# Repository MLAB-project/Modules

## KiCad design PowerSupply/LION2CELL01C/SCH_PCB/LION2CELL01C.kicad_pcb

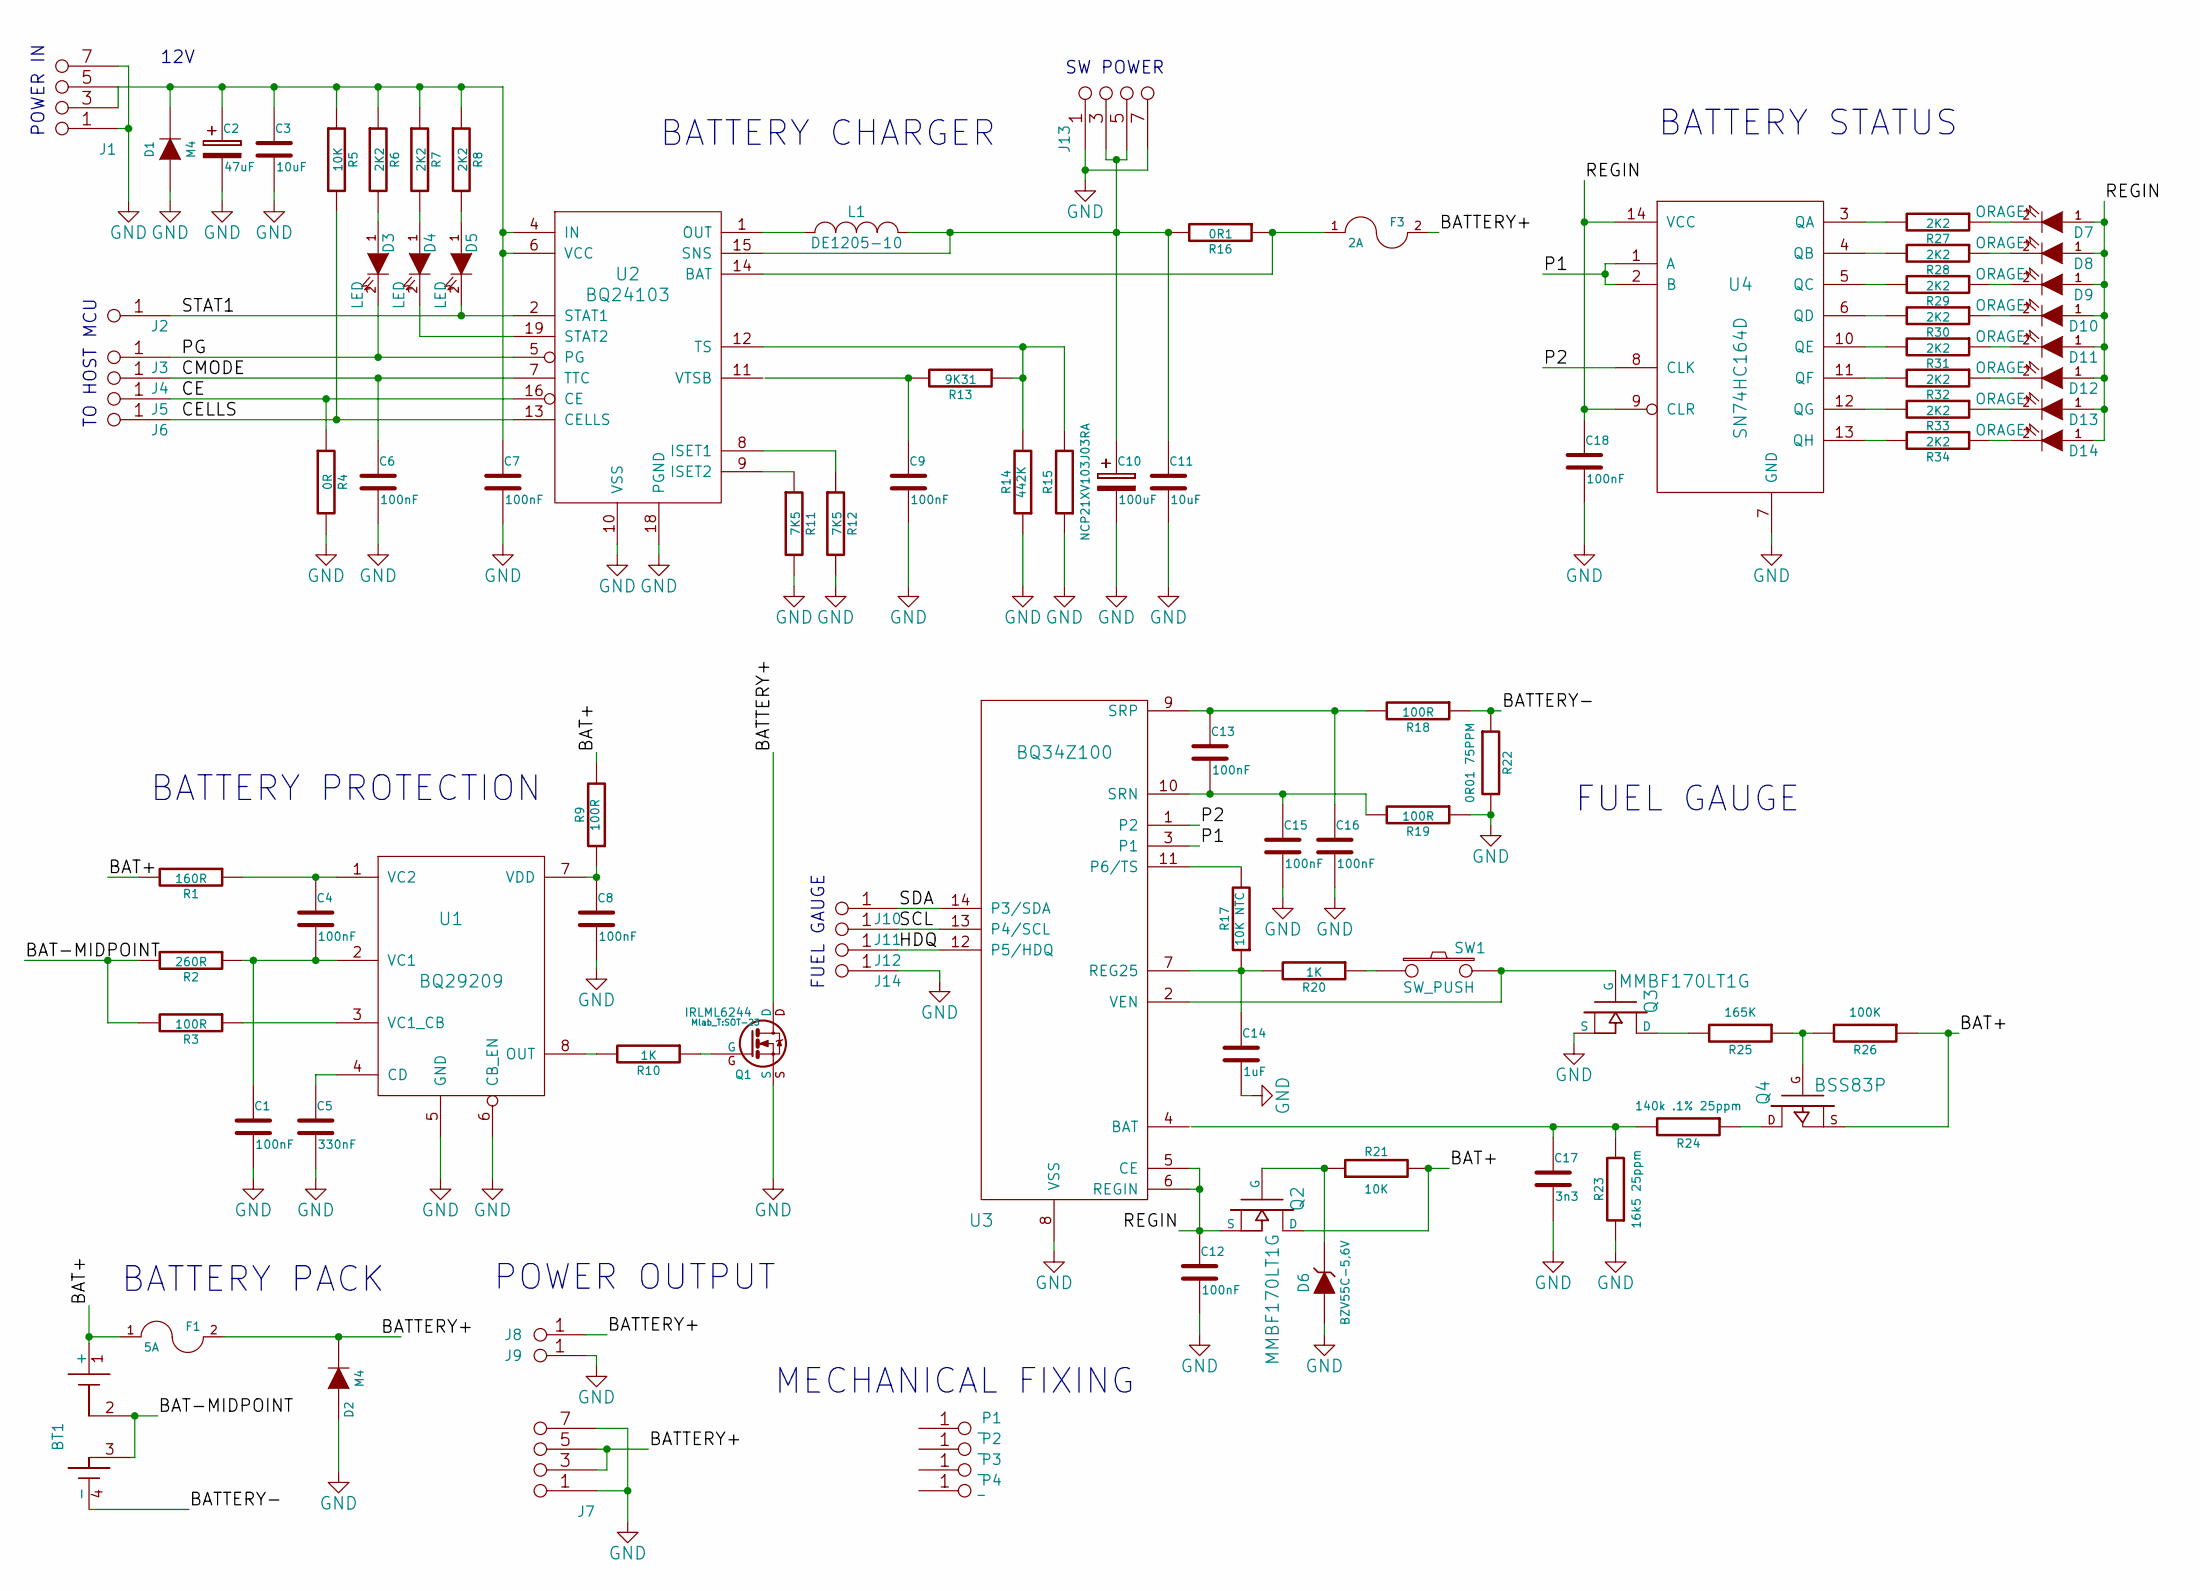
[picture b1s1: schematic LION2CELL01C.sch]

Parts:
BT1: 2x18650_LION-RESCUE-LION2CELL01C; 2LION
C1, C4, C6, C7, C8, C9, C12, C13, C15, C16, C18: 100nF; SMD-0805
C2: 47uF; TantalC_SizeC_Reflow
C3, C11: 10uF; SMD-0805
C5: 330nF; SMD-0805
C10: 100uF; TantalC_SizeD_Reflow
C14: 1uF; SMD-0805
C17: 3n3; SMD-0805
D1, D2: M4; SMA_Standard
D3, D4, D5: LED; LED_1206
D6: BZV55C-5,6V; MiniMELF_Standard
D7, D8, D9, D10, D11, D12, D13, D14: ORAGE; LED_1206
F1: 5A; Drzak_2410
F3: 2A; Drzak_2410
J1, J7, J13: JUMP_4X2; Straight_2x04
J2, J3, J4, J5, J6, J10, J11, J12, J14: JUMP_2x1; Straight_1x02
J8, J9: CONN1_1; WAGO256
L1: DE1205-10
P1, P2, P3, P4: _; MountingHole_3mm
Q1: IRLML6244; SOT-23
Q2, Q3: MMBF170LT1G; SOT-23
Q4: BSS83P; SOT-23
R1: 160R; SMD-0805
R2: 260R; SMD-0805
R3, R9, R18, R19: 100R; SMD-0805
R4: 0R; SMD-0805
R5, R21: 10K; SMD-0805
R6, R7, R8, R27, R28, R29, R30, R31, R32, R33, R34: 2K2; SMD-0805
R10, R20: 1K; SMD-0805
R11, R12: 7K5; SMD-0805
R13: 9K31; SMD-0805
R14: 442K; SMD-0805
R15: NCP21XV103J03RA; SMD-0805
R16: 0R1; R_2512
R17: 10K NTC; SMD-0805
R22: 0R01 75PPM; SMD-1206
R23: 16k5 25ppm; SMD-0805
R24: 140k .1% 25ppm; SMD-0805
R25: 165K; SMD-0805
R26: 100K; SMD-0805
SW1: SW_PUSH; SW_PUSH_SMALL
U1: BQ29209; VSON-8
U2: BQ24103; VQFN-20
U3: BQ34Z100; TSSOP-14_4.4x5mm_Pitch0.65mm
U4: SN74HC164D; SO-14

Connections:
/BAT+: BT1.1 (+), F1.1, Q2.D, Q4.S, R1.2, R9.2, R21.2, R26.1
/BAT-MIDPOINT: BT1.2, BT1.3, R2.2, R3.2
/BATTERY+: D2.2 (K), F1.2, F3.2, J7.3 (4), J7.4, J7.5, J7.6 (5), J8.1, Q1.D
/BATTERY-: BT1.4 (-), R18.1, R22.1
/CE: J5.1, J5.2, R4.1, U2.16 (CE)
/CELLS: J6.1, J6.2, R5.2, U2.13 (CELLS)
/CMODE: C6.1, J4.1, J4.2, U2.7 (TTC)
/HDQ: J12.1, J12.2, U3.12 (P5/HDQ)
/P1: U3.3 (P1), U4.1 (A), U4.2 (B)
/P2: U3.1 (P2), U4.8 (CLK)
/PG: D3.2 (K), J3.1, J3.2, U2.5 (PG)
/REGIN: C12.1, C18.1, D7.1 (A), D8.1 (A), D9.1 (A), D10.1 (A), D11.1 (A), D12.1 (A), D13.1 (A), D14.1 (A), Q2.S, U3.5 (CE), U3.6 (REGIN), U4.9 (CLR), U4.14 (VCC)
/SCL: J11.1, J11.2, U3.13 (P4/SCL)
/SDA: J10.1, J10.2, U3.14 (P3/SDA)
/STAT1: D5.2 (K), J2.1, J2.2, U2.2 (STAT1)
GND: C1.2, C2.2, C3.2, C5.2, C6.2, C7.2, C8.2, C9.2, C10.2, C11.2, C12.2, C14.2, C15.2, C16.2, C17.2, C18.2, D1.1 (A), D2.1 (A), D6.1 (A), J1.1 (2), J1.2, J1.7 (8), J1.8, J7.1 (2), J7.2, J7.7 (8), J7.8, J9.1, J13.1 (2), J13.2, J13.7 (8), J13.8, J14.1, J14.2, Q1.S, Q3.S, R4.2, R11.2, R12.2, R14.1, R15.1, R19.1, R22.2, R23.1, U1.5 (GND), U1.6 (CB_EN), U1.9 (GND), U2.10 (VSS), U2.17 (PGND), U2.18 (PGND), U2.21 (pgnd), U3.8 (VSS), U4.7 (GND)
unnamed: C1.1, C4.2, R2.1, U1.2 (VC1)
unnamed: C2.1, C3.1, C7.1, D1.2 (K), J1.3 (4), J1.4, J1.5, J1.6 (5), R5.1, R6.1, R7.1, R8.1, U2.3 (IN), U2.4 (IN), U2.6 (VCC)
unnamed: C4.1, R1.1, U1.1 (VC2)
unnamed: C5.1, U1.4 (CD)
unnamed: C8.1, R9.1, U1.7 (VDD)
unnamed: C9.1, R13.2
unnamed: C10.1, C11.1, J13.3 (4), J13.4, J13.5, J13.6 (5), L1.2, R16.2, U2.15 (SNS)
unnamed: C13.1, C16.1, R18.2, U3.9 (SRP)
unnamed: C13.2, C15.1, R19.2, U3.10 (SRN)
unnamed: C14.1, R17.1, R20.2, U3.7 (REG25)
unnamed: C17.1, R23.2, R24.2
unnamed: D3.1 (A), R6.2
unnamed: D4.1 (A), R7.2
unnamed: D4.2 (K), U2.19 (STAT2)
unnamed: D5.1 (A), R8.2
unnamed: D6.2 (K), Q2.G, R21.1
unnamed: D7.2 (K), R27.1
unnamed: D8.2 (K), R28.1
unnamed: D9.2 (K), R29.1
unnamed: D10.2 (K), R30.1
unnamed: D11.2 (K), R31.1
unnamed: D12.2 (K), R32.1
unnamed: D13.2 (K), R33.1
unnamed: D14.2 (K), R34.1
unnamed: F3.1, R16.1, U2.14 (BAT)
unnamed: L1.1, U2.1 (OUT), U2.20 (OUT)
unnamed: Q1.G, R10.1
unnamed: Q3.D, R25.2
unnamed: Q3.G, SW1.2, U3.2 (VEN)
unnamed: Q4.D, R24.1
unnamed: Q4.G, R25.1, R26.2
unnamed: R3.1, U1.3 (VC1_CB)
unnamed: R10.2, U1.8 (OUT)
unnamed: R11.1, U2.9 (ISET2)
unnamed: R12.1, U2.8 (ISET1)
unnamed: R13.1, R14.2, R15.2, U2.12 (TS)
unnamed: R17.2, U3.11 (P6/TS)
unnamed: R20.1, SW1.1
unnamed: R27.2, U4.3 (QA)
unnamed: R28.2, U4.4 (QB)
unnamed: R29.2, U4.5 (QC)
unnamed: R30.2, U4.6 (QD)
unnamed: R31.2, U4.10 (QE)
unnamed: R32.2, U4.11 (QF)
unnamed: R33.2, U4.12 (QG)
unnamed: R34.2, U4.13 (QH)

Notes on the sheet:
BATTERY PACK
BATTERY CHARGER
SW POWER
POWER IN
TO HOST MCU
BATTERY PROTECTION
FUEL GAUGE
POWER OUTPUT
MECHANICAL FIXING
BATTERY STATUS
12V

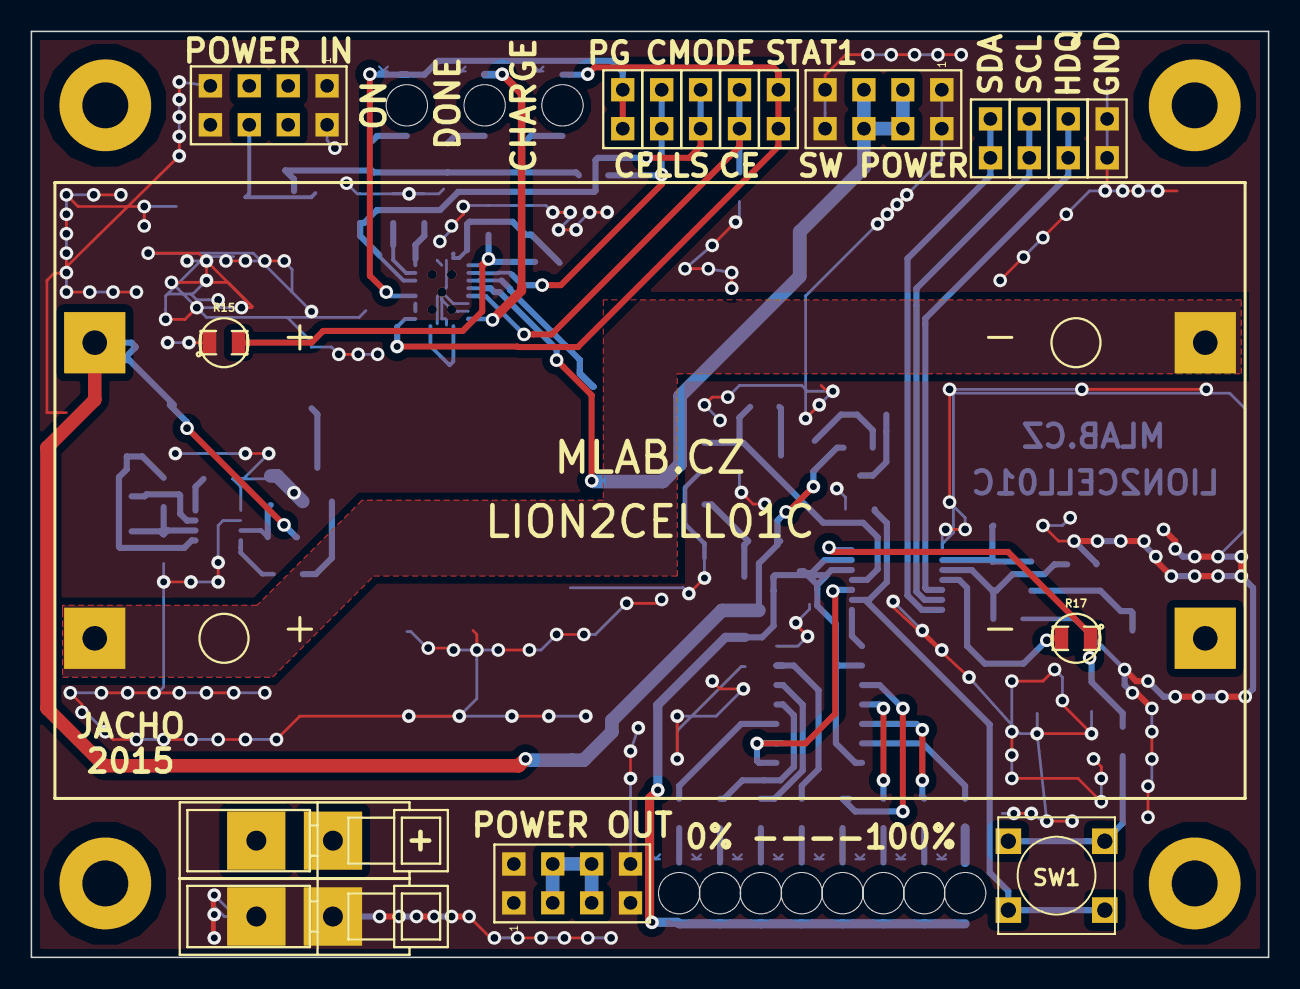
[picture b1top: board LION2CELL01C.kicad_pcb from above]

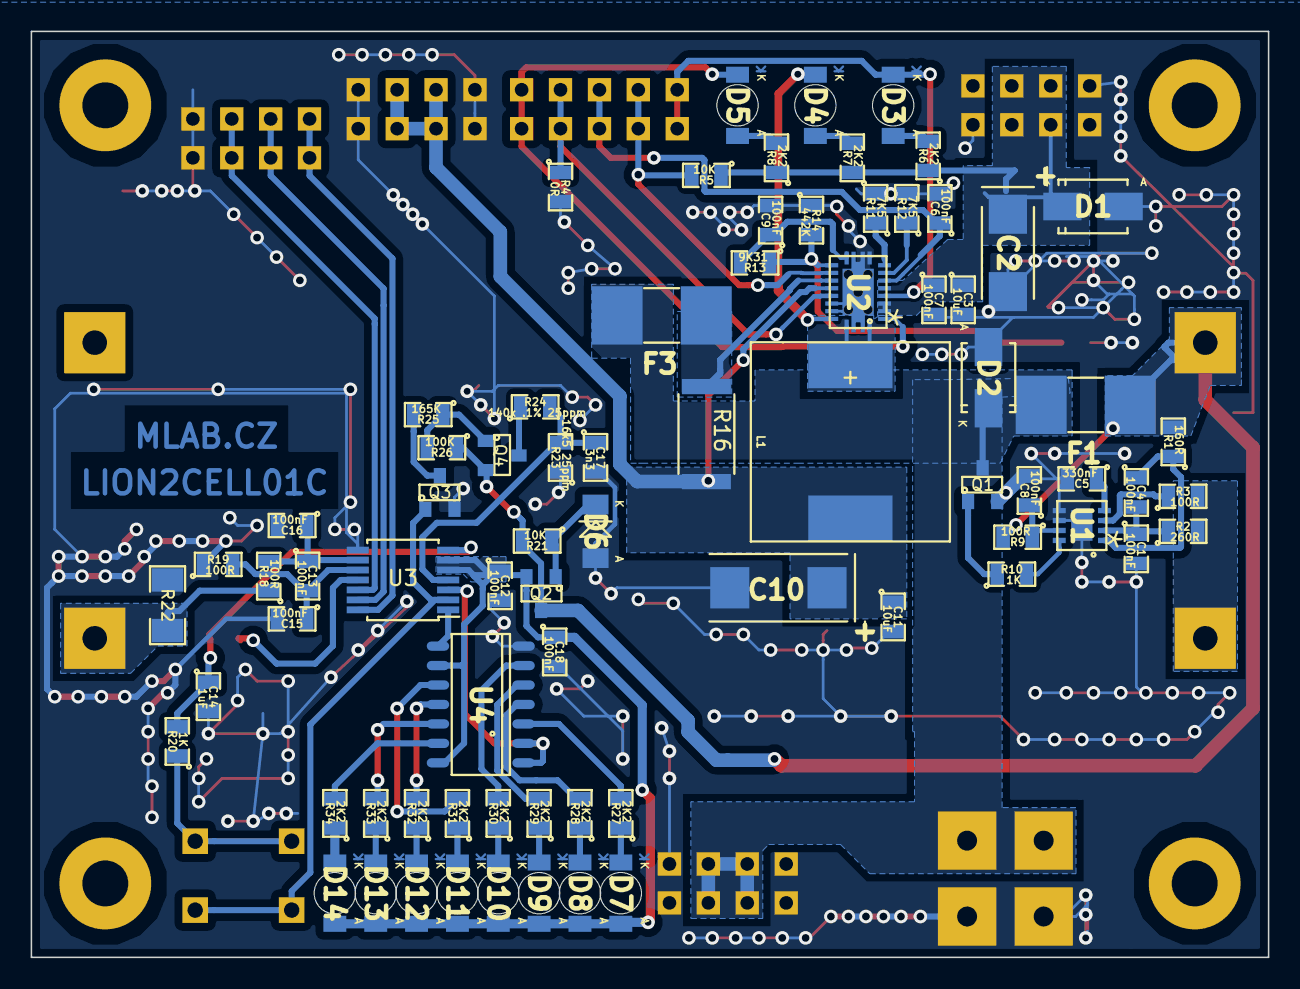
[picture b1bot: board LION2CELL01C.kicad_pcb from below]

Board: 2 copper layers, 80.8 x 60.5 mm, 97 parts (75 on the bottom side), 62 nets.

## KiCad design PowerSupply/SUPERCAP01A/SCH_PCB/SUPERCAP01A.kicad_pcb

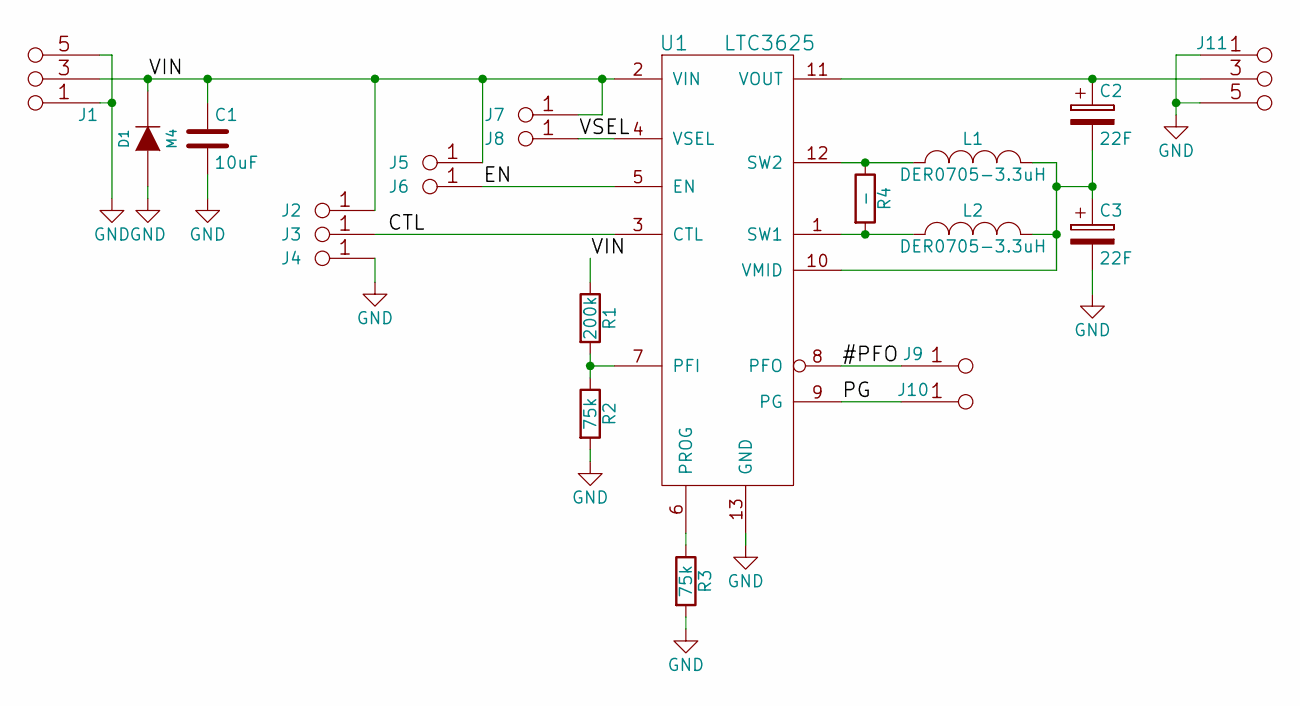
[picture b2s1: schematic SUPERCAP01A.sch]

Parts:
C1: 10uF; SMD-0805
C2, C3: 22F; C_Radial_D16_L25_P7.5
D1: M4; SMA_Standard
J1, J11: JUMP_3X2; Straight_2x03
J2, J3, J4, J5, J6, J7, J8: CONN1_1; Straight_1x01
J9, J10: JUMP_2x1; Straight_2x01
L1, L2: DER0705-3.3uH; DER0705
R1: 200k; SMD-0805
R2, R3: 75k; SMD-0805
R4: -; SMD-0805
U1: LTC3625

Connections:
/#PFO: J9.1, J9.2, U1.8 (PFO)
/CTL: J3.1, U1.3 (CTL)
/EN: J6.1, U1.5 (EN)
/PG: J10.1, J10.2, U1.9 (PG)
/VIN: C1.1, D1.2 (K), J1.3 (4), J1.4, J2.1, J5.1, J7.1, R1.1, U1.2 (VIN)
/VSEL: J8.1, U1.4 (VSEL)
GND: C1.2, C3.2, D1.1 (A), J1.1 (2), J1.2, J1.5 (6), J1.6, J4.1, J11.1 (2), J11.2, J11.5 (6), J11.6, R2.2, R3.2, U1.13 (GND); also elsewhere on the board
unnamed 7: C2.1, J11.3 (4), J11.4, U1.11 (VOUT); also elsewhere on the board
unnamed: C2.2, C3.1, L1.2, L2.2, U1.10 (VMID)
unnamed: L1.1, R4.1, U1.12 (SW2)
unnamed: L2.1, R4.2, U1.1 (SW1)
unnamed: R1.2, R2.1, U1.7 (PFI)
unnamed: R3.1, U1.6 (PROG)

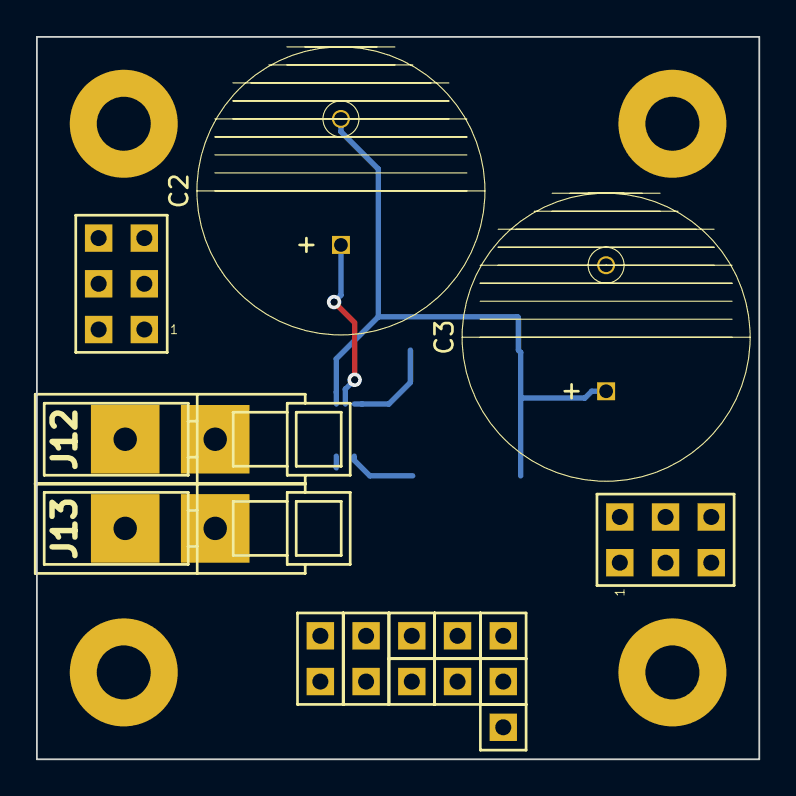
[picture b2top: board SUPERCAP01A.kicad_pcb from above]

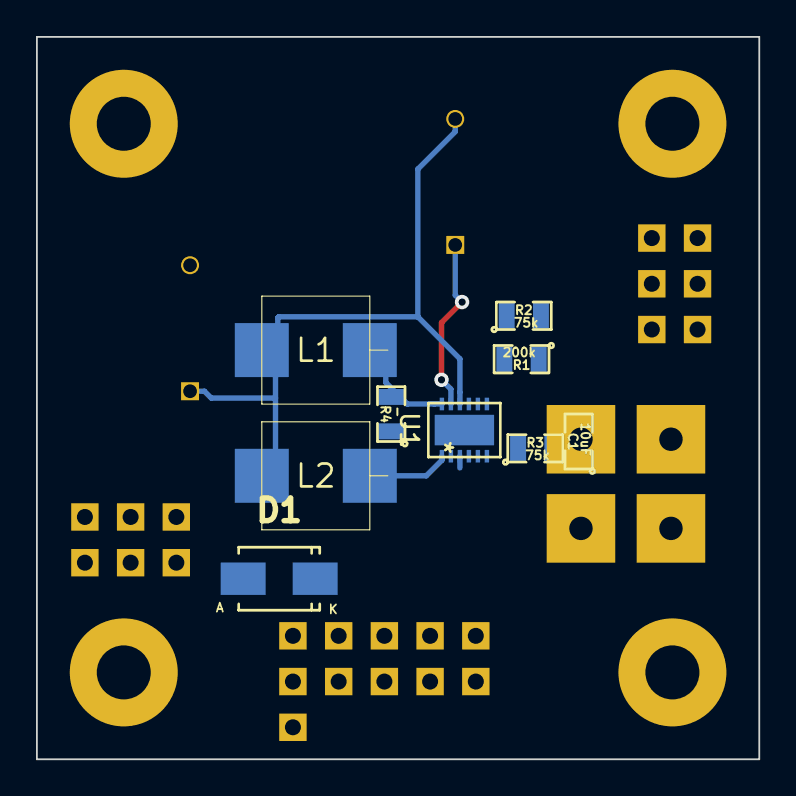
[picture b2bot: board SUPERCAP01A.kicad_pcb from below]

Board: 2 copper layers, 40.1 x 40.1 mm, 28 parts (9 on the bottom side), 13 nets.

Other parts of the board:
J12, J13: CONN1_1; WAGO256
M1, M2, M3, M4: HOLE; MountingHole_3mm

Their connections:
GND: J13.1; also elsewhere on the board
unnamed 7: J12.1; also elsewhere on the board

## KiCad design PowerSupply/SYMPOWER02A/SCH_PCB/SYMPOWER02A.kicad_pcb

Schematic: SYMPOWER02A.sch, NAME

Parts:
C1, C14, C15: NFM21PC105; FIR1
C2, C7, C12, C13: 10uF; SMD-0805
C3, C6, C10, C11: 1uF; SMD-0805
C4, C5, C8, C9, C16, C17: 100nF; SMD-0805
D1: M4; SMA_Standard
J1: HEADER_2x03_PARALLEL; Straight_2x03
J2, J3, J4: HEADER_2x01_PARALLEL; Straight_2x01
J5: HEADER_2x05_PARALLEL; Straight_2x05
M1, M2, M3, M4: HOLE; MountingHole_3mm
R1, R2: 10k; SMD-0805
R3: 100k; SMD-0805
R4: 210k; SMD-0805
R5, R6: 120k; SMD-0805
R7: 210; SMD-0805
R8: 1k; SMD-0805
U1: LM27762; WSON-12

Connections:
/C1+: C5.1, C6.1, U1.10 (C1+)
/C1-: C5.2, C6.2, U1.9 (C1-)
/CP: C7.1, C17.2, U1.5 (CP)
/EN+: J2.1, J2.2, R1.2, U1.12 (EN+)
/EN-: J3.1, J3.2, R2.2, U1.8 (EN-)
/FB+: R4.2, R5.1, U1.2 (FB+)
/FB-: R6.2, R7.1, U1.7 (FB-)
/PGOOD: J4.1, J4.2, R3.2, U1.1 (PGOOD)
/Vout+: C14.3, J5.5, J5.6, R4.1
/Vout-: C15.3, J5.3, J5.4, J5.7, J5.8, R7.2
GND: C1.2, C2.2, C3.2, C4.2, C7.2, C8.2, C9.1, C10.2, C11.1, C12.2, C13.1, C14.2, C15.2, C16.2, C17.1, D1.2, J1.1, J1.2, J1.5, J1.6, J5.1, J5.2, J5.9, J5.10, R5.2, R6.1, R8.2, U1.4 (GND), U1.13 (TP)
unnamed: C1.1, D1.1, J1.3, J1.4
unnamed: C8.1, C10.1, C12.1, C14.1, U1.11 (OUT+)
unnamed: C9.2, C11.2, C13.2, C15.1, U1.6 (OUT-)
unnamed: C16.1, M1.1, M2.1, M3.1, M4.1, R8.1
VCC: C1.3, C2.1, C3.1, C4.1, R1.1, R2.1, R3.1, U1.3 (VIN)

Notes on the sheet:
MOUNTING HOLES
For Uout 5V R5,R6 - 150k R4,R7 - 475k

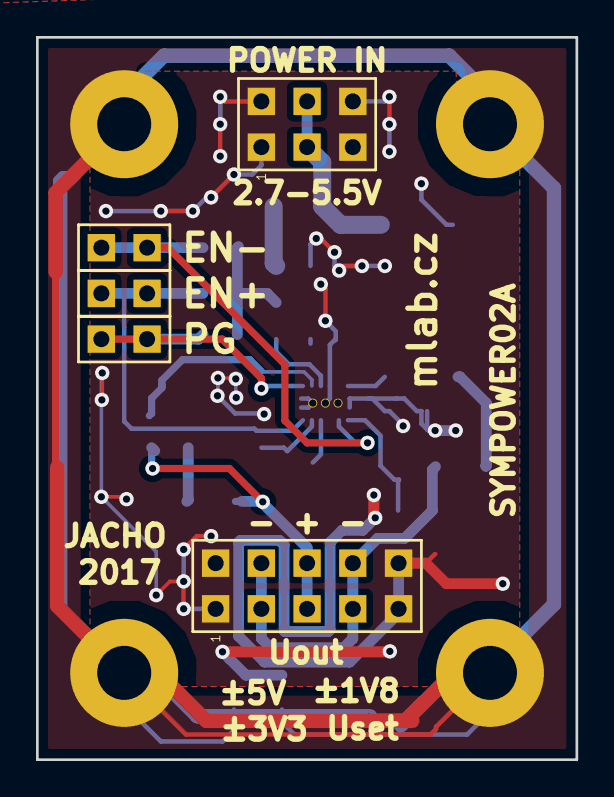
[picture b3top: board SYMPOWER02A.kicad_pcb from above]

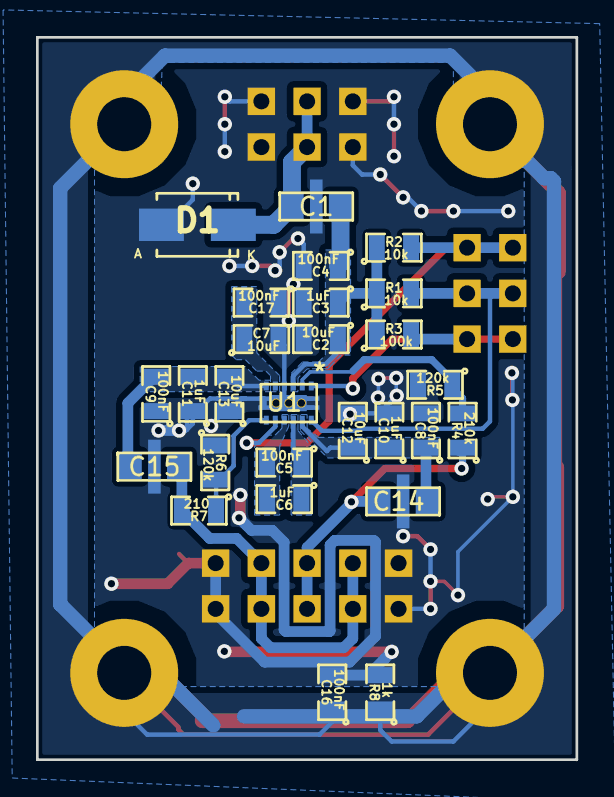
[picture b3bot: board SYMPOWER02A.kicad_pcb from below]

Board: 2 copper layers, 30.0 x 40.1 mm, 36 parts (27 on the bottom side), 16 nets.

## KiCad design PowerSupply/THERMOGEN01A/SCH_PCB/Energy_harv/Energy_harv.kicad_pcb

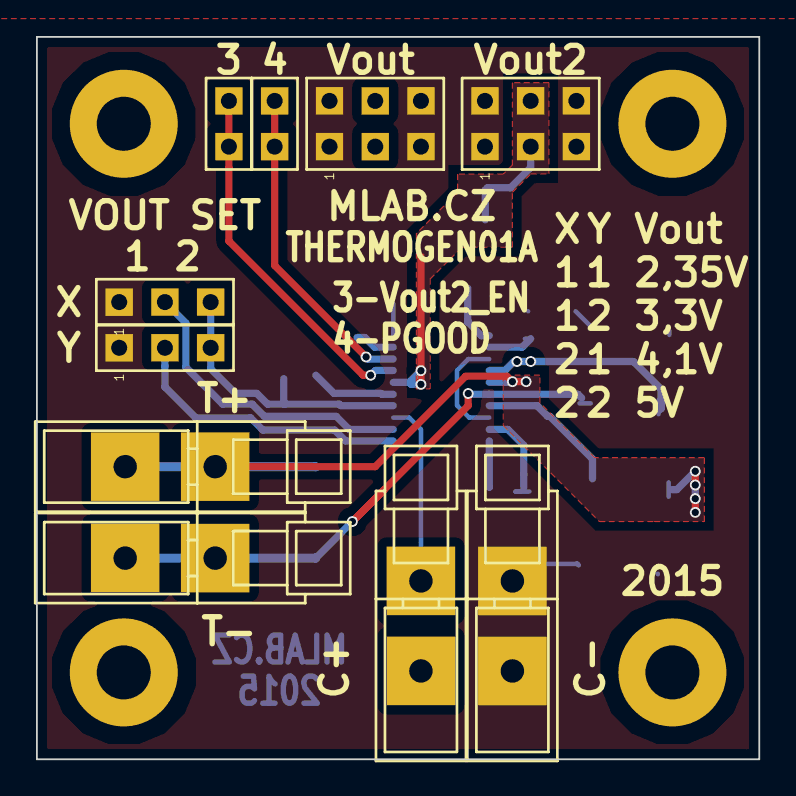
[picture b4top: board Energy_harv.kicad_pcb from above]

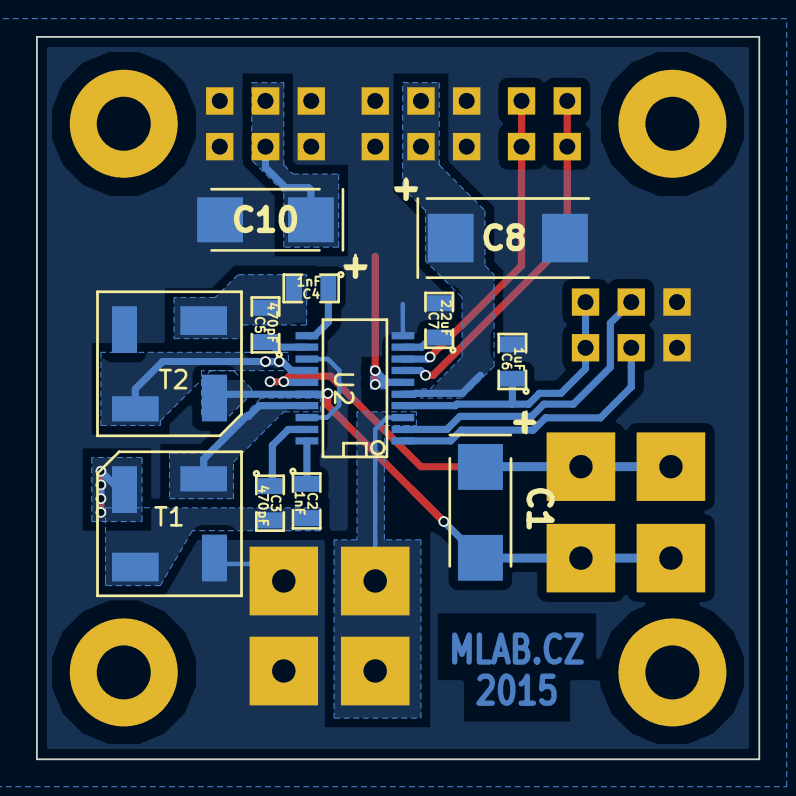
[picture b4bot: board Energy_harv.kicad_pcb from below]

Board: 2 copper layers, 40.1 x 40.1 mm, 26 parts (12 on the bottom side), 20 nets.

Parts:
C1, C10: 47uF; TantalC_SizeC_Reflow
C2, C4: 1nF; SMD-0805
C3, C5: 470pF; SMD-0805
C6: 1uF; SMD-0805
C7: 2,2uF; SMD-0805
C8: 470uF; TantalC_SizeD_Reflow
J1, J2: JUMP1X3; Straight_1x03
J3, J4: JUMP1X2; Straight_1x02
J5, J6: JUMP2X3; Straight_2x03
M1, M2, M3, M4: HOLE; MountingHole_3mm
P1, P2, P3, P4: WAGO256
T1, T2: Step-Up_TRANSFO; Step-Up_TRANSF
U2: LTC3109GN; SSOP-20

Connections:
/C+: P4.1, U2.3
/PGOOD: J4.1, J4.2, U2.8
/T+: C1.1, P1.1, T1.1, U2.15
/T-: C1.2, P2.1, T2.1, U2.16
/VAUX: C6.1, J1.3, J2.3, U2.4
/VOUT2_EN: J3.1, J3.2, U2.7
/VS1: J1.2, U2.1
/VS2: J2.2, U2.2
/V_OUT: C8.1, J6.3, J6.4, U2.5
/V_OUT2: C10.1, J5.3, J5.4, U2.6
GND: C6.2, C7.2, C8.2, C10.2, J1.1, J2.1, J5.1, J5.2, J5.5, J5.6, J6.1, J6.2, J6.5, J6.6, P3.1, T1.3, T2.3, U2.10, U2.13, U2.18
unnamed: C2.1, U2.20
unnamed: C2.2, C3.2, T1.4
unnamed: C3.1, U2.19
unnamed: C4.1, U2.11
unnamed: C4.2, C5.2, T2.4
unnamed: C5.1, U2.12
unnamed: C7.1, U2.9
unnamed: T1.2, U2.17
unnamed: T2.2, U2.14

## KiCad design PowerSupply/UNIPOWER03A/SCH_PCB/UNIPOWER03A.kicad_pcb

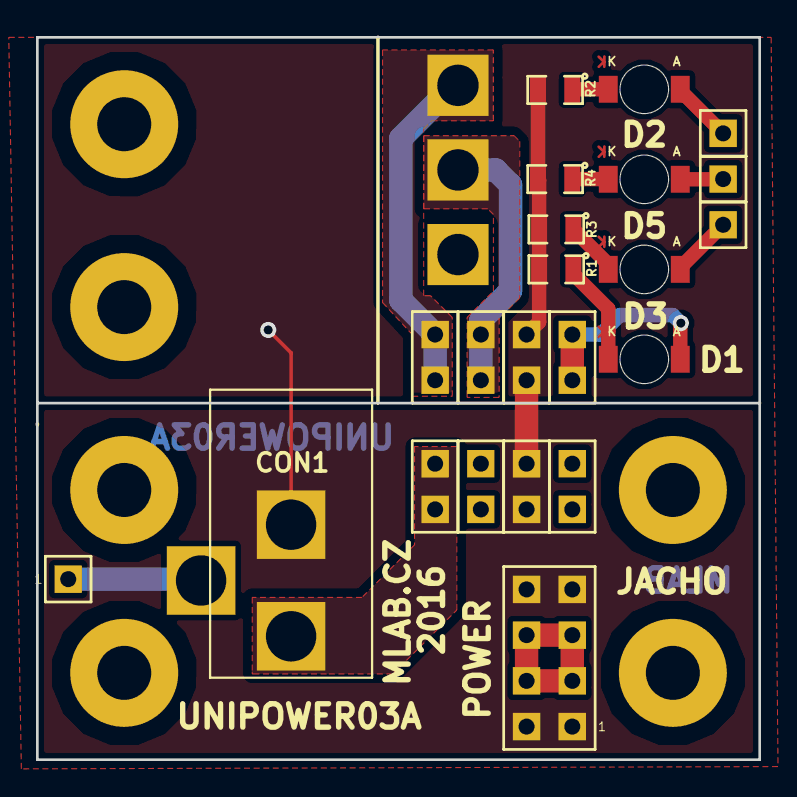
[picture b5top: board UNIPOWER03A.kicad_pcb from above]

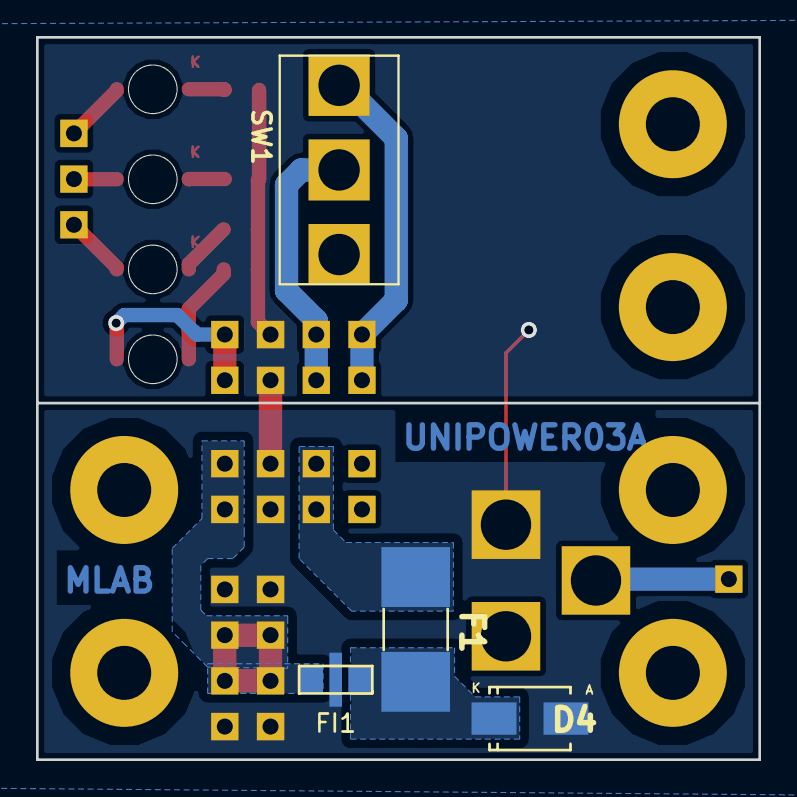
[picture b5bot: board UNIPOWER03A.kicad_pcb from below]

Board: 2 copper layers, 40.1 x 40.1 mm, 32 parts (4 on the bottom side), 16 nets.

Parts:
CON1: JACK_DC2.1; DC2,1MM
D1, D2, D3, D5: LED; LED_1206
D4: D; Diode-SMA_Standard
F1: F_Small; Drzak_2410
FI1: EMI_FILTER; FIR1
J1, J2, J4, J5: CONN1_2; Straight_1x02
J3, J9, J10, J11: JUMP_2x1; Straight_1x02
J6, J7, J12, J13: CONN1_1; Straight_1x01
J8: JUMP_4X2; Straight_2x04
M1, M2, M3, M4, M5, M8: HOLE; MountingHole_3mm
R1, R2, R3, R4: R; SMD-0805
SW1: Prepinac; Prepinaci_3A_SL19121

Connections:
GND: CON1.2, D4.2, FI1.2, J8.1, J8.2, J8.7, J8.8, J10.1, J10.2, J11.1, J11.2, R1.2, R2.2, R3.2, R4.2
unnamed: CON1.1, J1.1, J1.2
unnamed: CON1.3, J13.1
unnamed: D1.1, R1.1
unnamed: D1.2, J9.1, J9.2
unnamed: D2.1, R2.1
unnamed: D2.2, J6.1
unnamed: D3.1, R3.1
unnamed: D3.2, J7.1
unnamed: D4.1, F1.2, FI1.1
unnamed: D5.1, R4.1
unnamed: D5.2, J12.1
unnamed: F1.1, J5.1, J5.2
unnamed: J2.1, J2.2, SW1.1
unnamed: J4.1, J4.2, SW1.2
VCC: FI1.3, J3.1, J3.2, J8.3, J8.4, J8.5, J8.6

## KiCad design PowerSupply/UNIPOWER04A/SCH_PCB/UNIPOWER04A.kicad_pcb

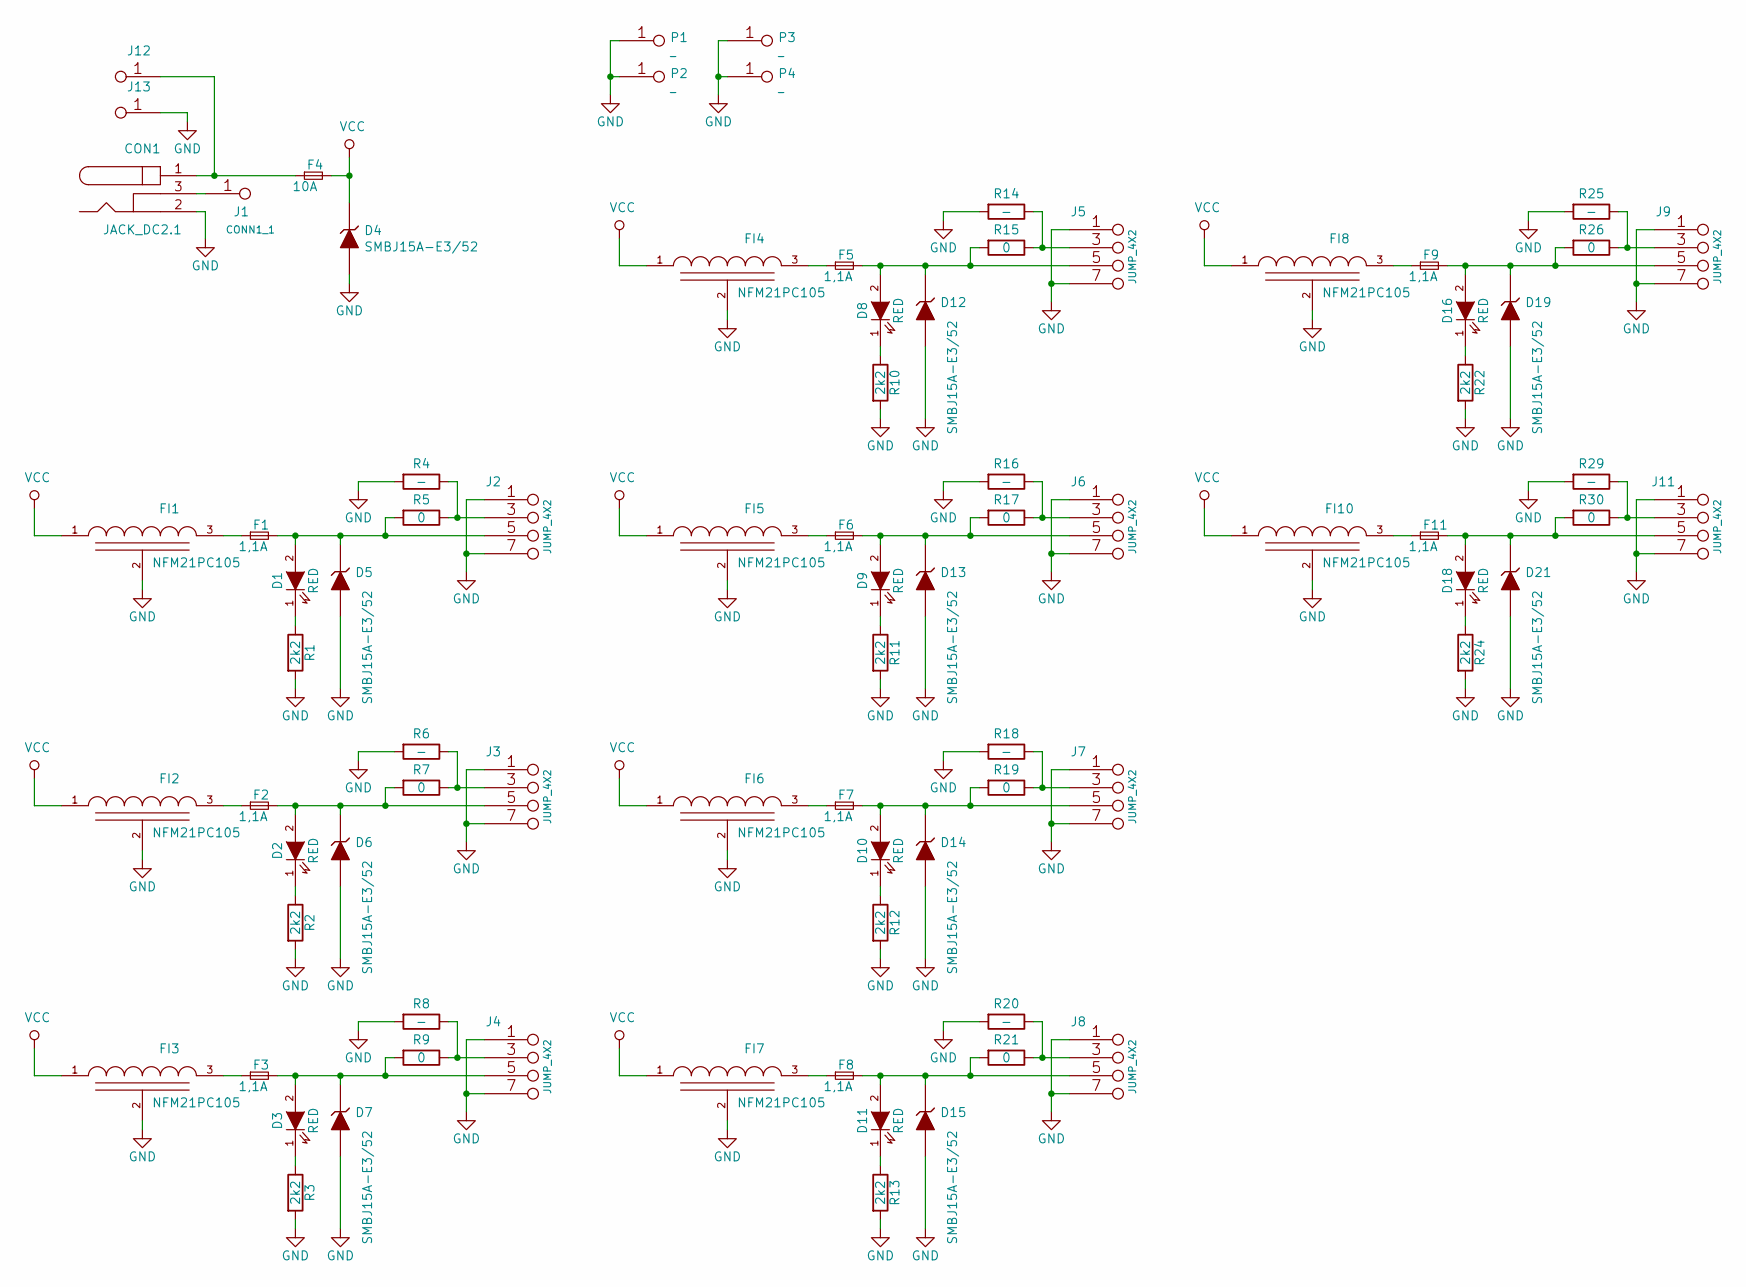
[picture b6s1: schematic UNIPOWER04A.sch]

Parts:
CON1: JACK_DC2.1; DC2,1MM
D1, D2, D3, D8, D9, D10, D11, D16, D18: RED; LED_1206
D4, D5, D6, D7, D12, D13, D14, D15, D19, D21: SMBJ15A-E3/52; SMB_Standard
F1, F2, F3, F5, F6, F7, F8, F9, F11: 1,1A; 2410
F4: 10A; Drzak_2410
FI1, FI2, FI3, FI4, FI5, FI6, FI7, FI8, FI10: NFM21PC105; FIR1
J1: CONN1_1; Straight_1x01
J2, J3, J4, J5, J6, J7, J8, J9, J11: JUMP_4X2; Straight_2x04
J12, J13: CONN1_1; WAGO256
P1, P2, P3, P4: _; MountingHole_3mm
R1, R2, R3, R10, R11, R12, R13, R22, R24: 2k2; SMD-0805
R4, R6, R8, R14, R16, R18, R20, R25, R29: -; SMD-0805
R5, R7, R9, R15, R17, R19, R21, R26, R30: 0; SMD-0805

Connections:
GND: CON1.2, D4.2 (A), D5.2 (A), D6.2 (A), D7.2 (A), D12.2 (A), D13.2 (A), D14.2 (A), D15.2 (A), D19.2 (A), D21.2 (A), FI1.2 (GND), FI2.2 (GND), FI3.2 (GND), FI4.2 (GND), FI5.2 (GND), FI6.2 (GND), FI7.2 (GND), FI8.2 (GND), FI10.2 (GND), J2.1 (2), J2.2, J2.7 (8), J2.8, J3.1 (2), J3.2, J3.7 (8), J3.8, J4.1 (2), J4.2, J4.7 (8), J4.8, J5.1 (2), J5.2, J5.7 (8), J5.8, J6.1 (2), J6.2, J6.7 (8), J6.8, J7.1 (2), J7.2, J7.7 (8), J7.8, J8.1 (2), J8.2, J8.7 (8), J8.8, J9.1 (2), J9.2, J9.7 (8), J9.8, J11.1 (2), J11.2, J11.7 (8), J11.8, J13.1, P1.1, P2.1, P3.1, P4.1, R1.2, R2.2, R3.2, R4.2, R6.2, R8.2, R10.2, R11.2, R12.2, R13.2, R14.2, R16.2, R18.2, R20.2, R22.2, R24.2, R25.2, R29.2
unnamed: CON1.1, F4.1, J12.1
unnamed: CON1.3, J1.1
unnamed: D1.1 (K), R1.1
unnamed: D1.2 (A), D5.1 (K), F1.2, J2.5, J2.6 (5), R5.2
unnamed: D2.1 (K), R2.1
unnamed: D2.2 (A), D6.1 (K), F2.2, J3.5, J3.6 (5), R7.2
unnamed: D3.1 (K), R3.1
unnamed: D3.2 (A), D7.1 (K), F3.2, J4.5, J4.6 (5), R9.2
unnamed: D8.1 (K), R10.1
unnamed: D9.1 (K), R11.1
unnamed: D10.1 (K), R12.1
unnamed: D10.2 (A), D14.1 (K), F7.2, J7.5, J7.6 (5), R19.2
unnamed: D11.1 (K), R13.1
unnamed: D11.2 (A), D15.1 (K), F8.2, J8.5, J8.6 (5), R21.2
unnamed: D8.2 (A), D12.1 (K), F5.2, J5.5, J5.6 (5), R15.2
unnamed: D9.2 (A), D13.1 (K), F6.2, J6.5, J6.6 (5), R17.2
unnamed: D16.1 (K), R22.1
unnamed: D16.2 (A), D19.1 (K), F9.2, J9.5, J9.6 (5), R26.2
unnamed: D18.1 (K), R24.1
unnamed: D18.2 (A), D21.1 (K), F11.2, J11.5, J11.6 (5), R30.2
unnamed: F1.1, FI1.3 (VO)
unnamed: F2.1, FI2.3 (VO)
unnamed: F3.1, FI3.3 (VO)
unnamed: F5.1, FI4.3 (VO)
unnamed: F6.1, FI5.3 (VO)
unnamed: F7.1, FI6.3 (VO)
unnamed: F8.1, FI7.3 (VO)
unnamed: F9.1, FI8.3 (VO)
unnamed: F11.1, FI10.3 (VO)
unnamed: J2.3 (4), J2.4, R4.1, R5.1
unnamed: J3.3 (4), J3.4, R6.1, R7.1
unnamed: J4.3 (4), J4.4, R8.1, R9.1
unnamed: J5.3 (4), J5.4, R14.1, R15.1
unnamed: J6.3 (4), J6.4, R16.1, R17.1
unnamed: J7.3 (4), J7.4, R18.1, R19.1
unnamed: J8.3 (4), J8.4, R20.1, R21.1
unnamed: J9.3 (4), J9.4, R25.1, R26.1
unnamed: J11.3 (4), J11.4, R29.1, R30.1
VCC: D4.1 (K), F4.2, FI1.1 (VI), FI2.1 (VI), FI3.1 (VI), FI4.1 (VI), FI5.1 (VI), FI6.1 (VI), FI7.1 (VI), FI8.1 (VI), FI10.1 (VI)
